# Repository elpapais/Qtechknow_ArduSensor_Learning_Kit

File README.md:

Qtechknow_ArduSensor_Learning_Kit
=================================

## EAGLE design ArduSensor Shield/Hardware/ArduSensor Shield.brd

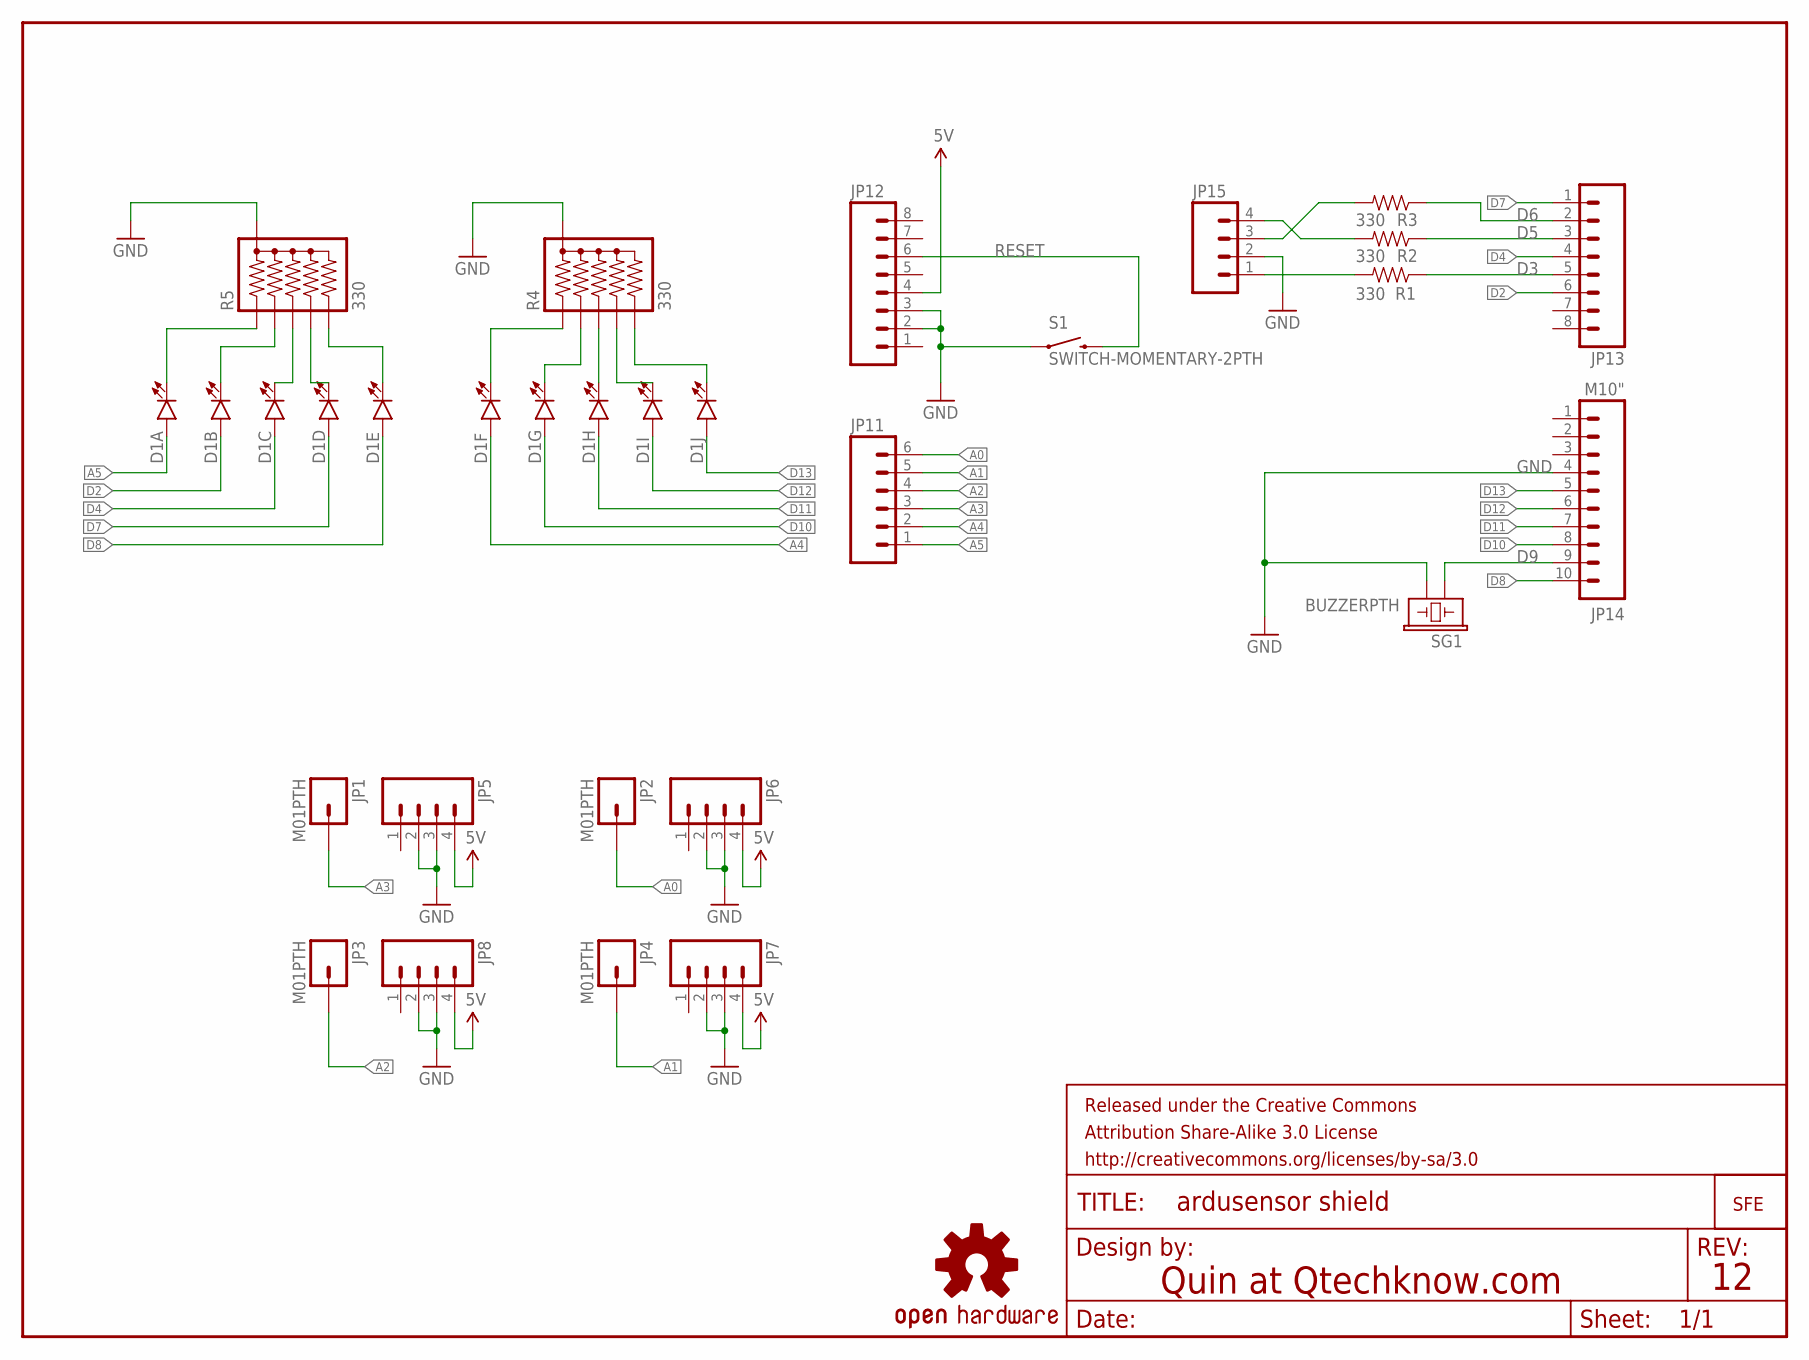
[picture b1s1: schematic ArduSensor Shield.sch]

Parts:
D1: LED_BARGRAPH_10; LED_BARGAPH_10
FRAME1: FRAME-LETTER; CREATIVE_COMMONS
JP1, JP2, JP3, JP4: M01PTH; 1X01
JP5, JP6, JP7, JP8, JP15: M04PTH; 1X04
JP9: LOGO-SFENEW; SFE-NEW-WEBLOGO
JP11: M06SIP; 1X06
JP12, JP13: M081X08; 1X08
JP14: M10"; 1X10
LOGO1: OSHW-LOGOM; OSHW-LOGO-M
R1, R2, R3: 330; 1/6W-RES
R4, R5: 330; RPACK-SIP-PTH-5
S1: SWITCH-MOMENTARY-2PTH; TACTILE-PTH
SG1: BUZZERPTH; BUZZER-12MM

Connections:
5V: JP5.4, JP6.4, JP7.4, JP8.4, JP12.4
A0: JP2.1, JP11.6
A1: JP4.1, JP11.5
A2: JP3.1, JP11.4
A3: JP1.1, JP11.3
A4: D1.6 (A), JP11.2
A5: D1.1 (A), JP11.1
D2: D1.2 (A), JP13.6
D3: JP13.5, R1.1
D4: D1.3 (A), JP13.4
D5: JP13.3, R2.1
D6: JP13.2, R3.1
D7: D1.4 (A), JP13.1
D8: D1.5 (A), JP14.10
D9: JP14.9, SG1.+ (1)
D10: D1.7 (A), JP14.8
D11: D1.8 (A), JP14.7
D12: D1.9 (A), JP14.6
D13: D1.10 (A), JP14.5
GND: JP5.2, JP5.3, JP6.2, JP6.3, JP7.2, JP7.3, JP8.2, JP8.3, JP12.2, JP12.3, JP14.4, JP15.2, R4.P$1 (1), R5.P$1 (1), S1.1, SG1.- (2)
unnamed: JP15.1, R1.2
unnamed: JP15.4, R2.2
unnamed: D1.11 (C), R4.P$6 (6)
unnamed: D1.12 (C), R4.P$5 (5)
unnamed: D1.13 (C), R4.P$4 (4)
unnamed: D1.14 (C), R4.P$3 (3)
unnamed: D1.15 (C), R4.P$2 (2)
unnamed: D1.16 (C), R5.P$6 (6)
unnamed: D1.17 (C), R5.P$5 (5)
unnamed: D1.18 (C), R5.P$4 (4)
unnamed: D1.19 (C), R5.P$3 (3)
unnamed: D1.20 (C), R5.P$2 (2)
unnamed: JP15.3, R3.2
RESET: JP12.6, S1.3 (2)

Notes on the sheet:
Quin at Qtechknow.com

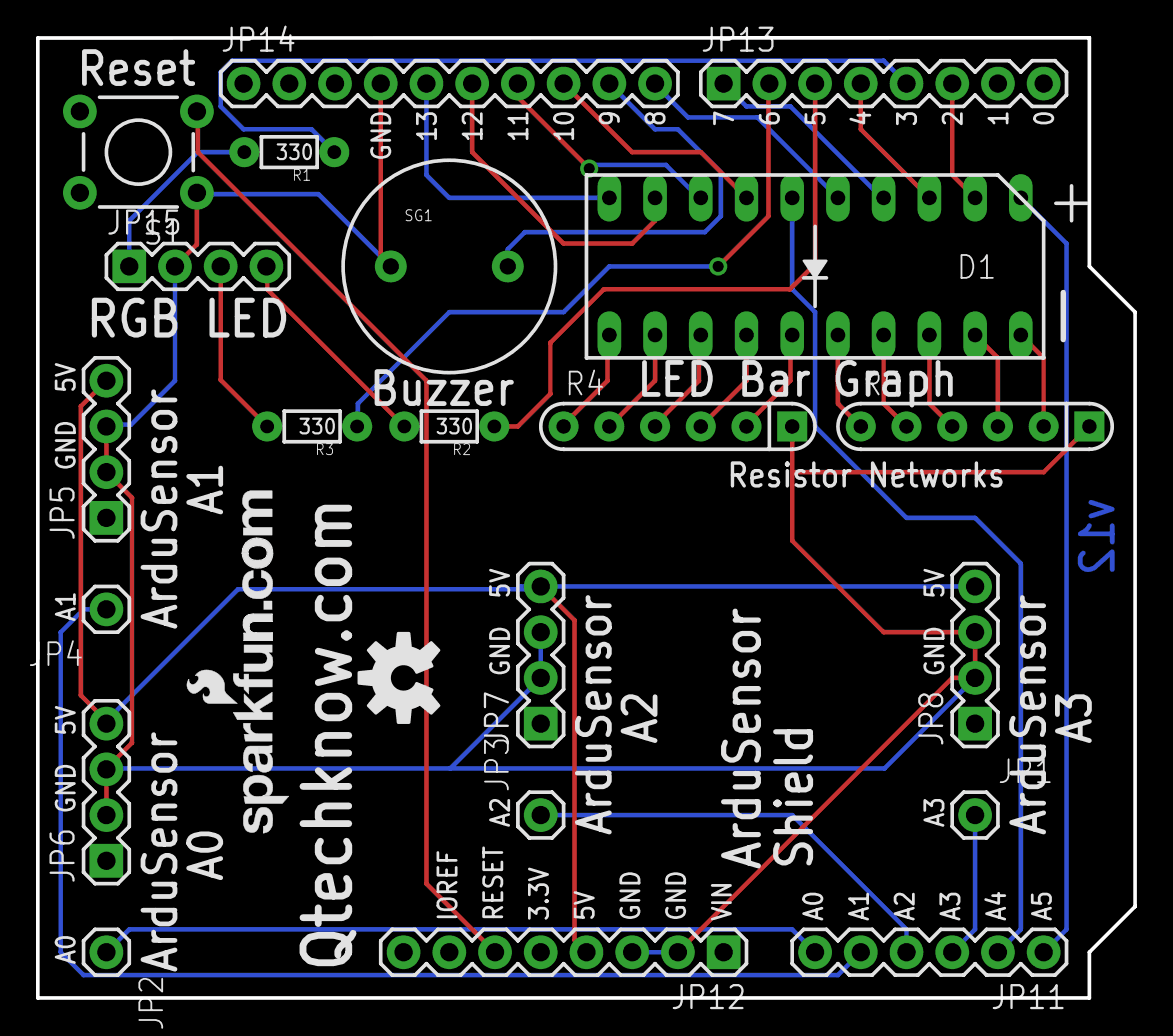
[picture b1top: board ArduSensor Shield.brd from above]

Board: 2 copper layers, 61.0 x 53.3 mm, 24 parts (0 on the bottom side), 34 nets.

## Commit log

2014-02-07 Initial board file commit
2014-02-08 Adding Shield hardware version 1.2

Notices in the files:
parts and their libraries:
SFE LED: Licensing: CC v3.0 Share-Alike You are welcome to use this library for commercial purposes.
SparkFun-Aesthetics: Released under the Creative Commons Attribution Share-Alike 3.0 License
SparkFun-Aesthetics: http://creativecommons.org/licenses/by-sa/3.0
